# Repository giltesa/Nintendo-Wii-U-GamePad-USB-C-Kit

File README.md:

# Nintendo Wii U GamePad: USB-C Kit

The **Nintendo Wii U GamePad: USB-C Kit** is a board that allows to replace the original power connector for a modern and standard USB-C.

**If your original connector / power supply is too old or damaged** and you need a new one, or **if you would like to power up your Nintendo Wii U GamePad with a standard USB-C charger**, such as the charger for your phone, or laptop, you can do so with this kit.

## Would you like it?

[**Nintendo Wii U GamePad: USB-C Kit**](https://shop.giltesa.com/?p=2799)

## License

This project is licensed under a **Creative Commons** license:
**[Attribution-NonCommercial-ShareAlike 4.0 International (CC BY-NC-SA 4.0) ](https://creativecommons.org/licenses/by-nc-sa/4.0/)**

Check the [LICENSE.md](LICENSE.md) for more information.

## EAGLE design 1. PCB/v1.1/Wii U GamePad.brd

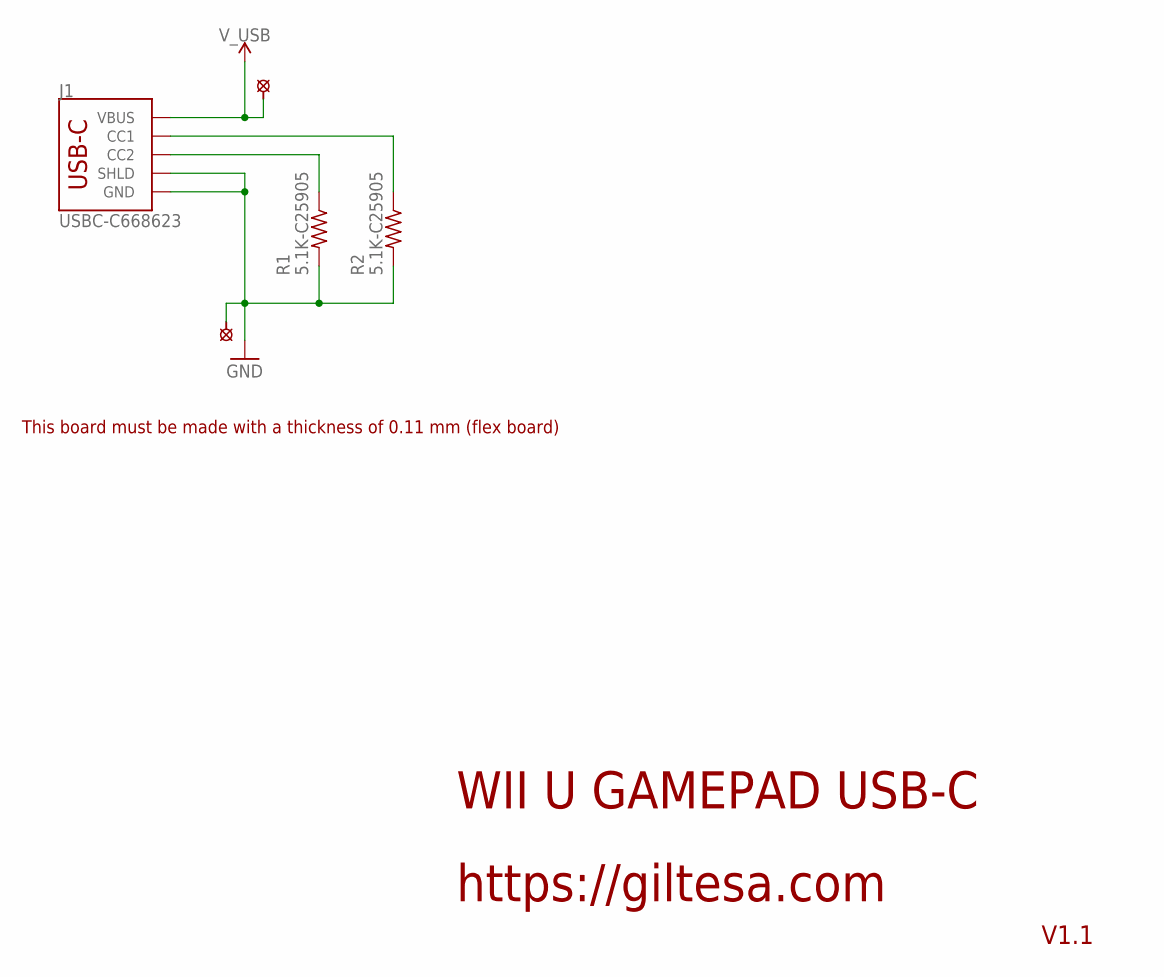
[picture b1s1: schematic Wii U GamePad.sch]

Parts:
J1: USBC-C668623; USB-C_6P_SMD_WIIU
R1, R2: 5.1K-C25905; R0402
U$1, U$2: PAD_1.7

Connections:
CC1: J1.A5 (CC1), R2.1
CC2: J1.B5 (CC2), R1.1
GND: J1.A12-GND (GND), J1.B12-GND (GND), J1.SHLD, R1.2, R2.2, U$2.P$1
V_USB: J1.A9-VBUS (VBUS), J1.B9-VBUS (VBUS), U$1.P$1

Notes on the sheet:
WII U GAMEPAD USB-C
https://giltesa.com
V1.1
This board must be made with a thickness of 0.11 mm (flex board)

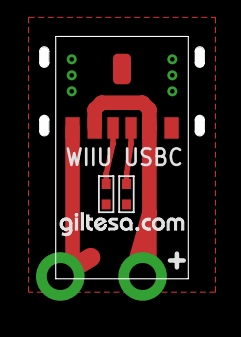
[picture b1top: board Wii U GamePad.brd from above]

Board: 2 copper layers, 9.1 x 13.5 mm, 6 parts (0 on the bottom side), 4 nets.

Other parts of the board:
U$11: GILTESA.COM_MASK_7MM

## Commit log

2024-11-15 no message
2025-08-01 v1.0
2025-08-01 v1.1

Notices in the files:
parts and their libraries:
SparkFun: Licensing: CC v3.0 Share-Alike You are welcome to use this library for commercial purposes.
SparkFun-PowerSymbols: Licensing: Creative Commons ShareAlike 4.0 International - https://creativecommons.org/licenses/by-sa/4.0
